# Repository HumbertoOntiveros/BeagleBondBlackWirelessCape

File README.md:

# BeagleBondBlackWirelessCape
A BeagleBone Black WIFI Cape
# Wi-Fi and BT/BLE connectivity Setup over SPI
## 1. Setup
### 1.1 Hardware Setup
In this setup, ESP board acts as a SPI peripheral and provides Wi-Fi capabilities to host. Please connect ESP peripheral to Beaglebone Black with jumper cables as mentioned below. It may be good to use small length cables to ensure signal integrity. Power ESP and BBB separately with a power supply that provide sufficient power. ESP can be powered through PC using micro-USB cable.

BBB pinout can be found [here!](https://beagleboard.org/support/bone101)

#### 1.1.1 ESP32 setup
| BBB pin label | BBB pin ID | ESP32 pin ID  | ESP32 pin function |
| --- | --- | --- | --- |
| P9_23 | 49 | 21 | GPIO_HANDSHAKE |
| P9_15 | 48 | 22 | GPIO_DATA_READY |
| SPI0_CS0 | P9_17 | 5 | CS |
| SPI0_SCLK | P9_22 | 18 | SCLK |
| SPI0_MISO D0 | P9_21 | 19 | MISO |
| SPI0_MOSI D1 | P9_18 | 23 | MOSI |
| P9_12 | 60 | RESET | RESET |

### 1.2 Beaglebone Black Software Setup
The SPI master driver is enabled by default on BBB OS. To disable it. 
```
cd host/linux/host_control/
./bbb_init.sh load_dtoverlay
```
the script will be update overlay for device tree to disable spi which used by default linux SPI driver.
The scrip will automatically reboot BBB after 10s to take effect. you could cancel.

## 2. Load ESP-Hosted Solution
### 2.1 Host Software
* Execute following commands in root directory of cloned ESP-Hosted repository on BBB
```sh
$ cd host/linux/host_control/
$ ./bbb_init.sh spi
```
* This script compiles and loads host driver on BBB. It also creates virtual serial interface `/dev/esps0` which is used as a control interface for Wi-Fi on ESP peripheral

### 2.2 ESP Peripheral Firmware
One can load pre-built release binaries on ESP peripheral or compile those from source. Below subsection explains Source Compilation methods due to this is a new commit for support BBB.

#### 2.2.1 Source Compilation
:warning:<code>Note: Please check [ESP-IDF Setup](Linux_based_readme.md#22-esp-idf-setup) and use appropriate ESP-IDF version</code>

* In root directory of ESP-Hosted repository, execute below command

```sh
$ cd esp/esp_driver/network_adapter
```

##### Using cmake

* :warning: `Set target if the ESP32-S2 or ESP32-C3 is being used. Skip if ESP32 is being used.`

```
$ idf.py set-target esp32
```
or
```
$ idf.py set-target esp32s2
```
or
```
$ idf.py set-target esp32c3
```

* Execute following command to configure project
```sh
$ idf.py menuconfig
```
* This will open project configuration window. To select SPI transport interface, navigate to `Example Configuration ->  Transport layer -> SPI interface -> select` and exit from menuconfig.

* For ESP32-C3, select chip revision in addition. Navigate to `Component config → ESP32C3-Specific → Minimum Supported ESP32-C3 Revision` and select chip version of ESP32-C3.

* Use below command to compile and flash the project. Replace <serial_port> with ESP peripheral's serial port.
```sh
$ idf.py -p <serial_port> build flash
```

## 3. Checking the Setup for SPI
Once ESP peripheral has a valid firmware and booted successfully, you should be able to see successful enumeration on BBB side as:
```
$ dmesg
[   96.439911] Bluetooth: Core ver 2.22
[   96.440145] NET: Registered protocol family 31
[   96.440153] Bluetooth: HCI device and connection manager initialized
[   96.440181] Bluetooth: HCI socket layer initialized
[   96.440195] Bluetooth: L2CAP socket layer initialized
[   96.440261] Bluetooth: SCO socket layer initialized
[  196.746813] esp32_spi: loading out-of-tree module taints kernel.
[  196.755748] esp_reset, ESP32: Resetpin of Host is 60
[  196.755892] esp_reset, ESP32: Triggering ESP reset.
[  196.775022] ESP32 peripheral is registered to SPI bus [0],chip select [0], SPI Clock [10]
[  199.310809] 
               Received INIT event from ESP32 peripheral
[  199.310839] EVENT: 2
[  199.310853] EVENT: 1
[  199.310857] EVENT: 0
[  199.310864] ESP peripheral capabilities: 0x78
[  200.155504] Bluetooth: BNEP (Ethernet Emulation) ver 1.3
[  200.155519] Bluetooth: BNEP filters: protocol multicast
[  200.155551] Bluetooth: BNEP socket layer initialized
[  200.699800] Bluetooth: RFCOMM TTY layer initialized
[  200.699842] Bluetooth: RFCOMM socket layer initialized
[  200.699906] Bluetooth: RFCOMM ver 1.11
```

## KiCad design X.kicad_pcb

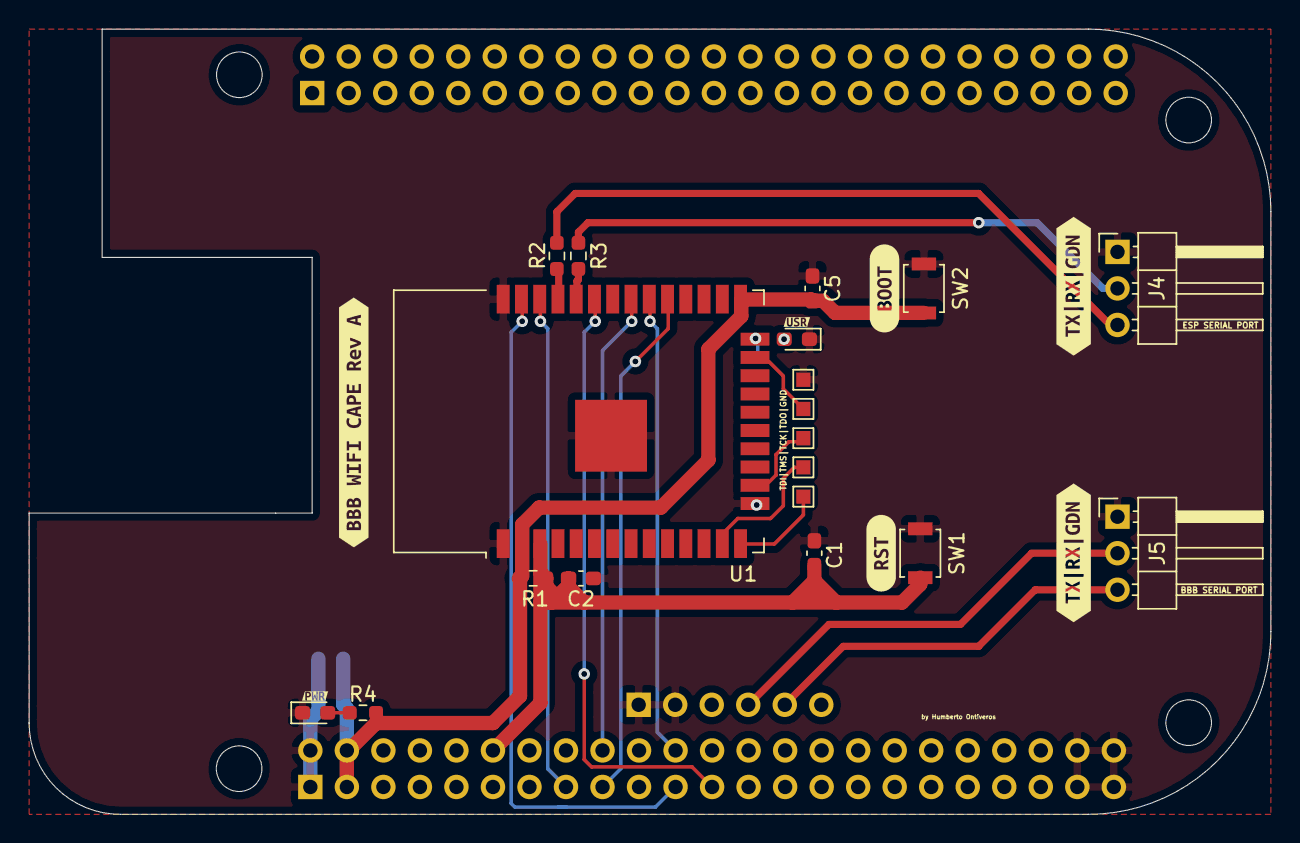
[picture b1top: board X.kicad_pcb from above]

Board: 2 copper layers, 86.4 x 54.6 mm, 33 parts (0 on the bottom side), 22 nets.

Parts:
C1, C2, C4, C5: 0.1uF(50v-10%); C_0603_1608Metric_Pad1.08x0.95mm_HandSolder
C3: 22uF(10V-20%); C_0603_1608Metric_Pad1.08x0.95mm_HandSolder
D1: POWER_LED; LED_0603_1608Metric_Pad1.05x0.95mm_HandSolder
D2: USER_LED; LED_0603_1608Metric_Pad1.05x0.95mm_HandSolder
J2: P8_CONN; BBB_CONN
J3: BBB_SP_CONN; PinSocket_1x06_P2.54mm_Vertical
J4: ESP_USB2TTL_CONN; PinHeader_1x03_P2.54mm_Horizontal
J5: BBB_USB2TTL_CONN; PinHeader_1x03_P2.54mm_Horizontal
J6: P9_CONN; BBB_CONN
R1, R6: 10K(5%); R_0603_1608Metric_Pad0.98x0.95mm_HandSolder
R2, R3: 0R(5%); R_0603_1608Metric_Pad0.98x0.95mm_HandSolder
R4, R5: 2K(5%); R_0603_1608Metric_Pad0.98x0.95mm_HandSolder
SW1: RST_SW
SW2: BOOT_SW; Boot_SW
TP1, TP2, TP3, TP4, TP5: TestPoint; TestPoint_Pad_1.0x1.0mm
U1: ESP32-WROOM-32D; ESP32-WROOM-32
kibuzzard-64DF0CF9, kibuzzard-64DF05EC, kibuzzard-64DF05EC#2, kibuzzard-64DF07FE, kibuzzard-64DF08E2, kibuzzard-64DF0500, kibuzzard-64DF0546: G***; label

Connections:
/IO2: R5.1, R6.2, U1.24
/TCK: TP3.1, U1.16
/TDI: TP4.1, U1.14
/TDO: TP2.1, U1.23
/TMS: TP5.1, U1.13
EN: C1.1, C2.1, J6.12, R1.2, SW1.2, U1.3
GND: C1.2, C2.2, C3.1, C4.1, C5.2, D1.1, D2.1, J3.1, J3.2, J4.1, J5.1, J6.1, J6.2, J6.43, J6.44, J6.45, J6.46, R6.1, SW1.1, SW2.2, TP1.1, U1.1, U1.15, U1.38, U1.39
GPIO_DATA_READY: J6.15, U1.36
GPIO_HANDSHAKE: J6.23, U1.33
IO0: C3.2, C4.2, C5.1, J6.3, J6.4, R1.1, R4.1, SW2.1, U1.2, U1.25
unnamed: D1.2, R4.2
unnamed: D2.2, R5.2
unnamed: J3.4, J5.2
unnamed: J3.5, J5.3
unnamed: R2.2, U1.35
unnamed: R3.2, U1.34
RXD: J4.2, R3.1
SPI0_CS0: J6.17, U1.29
SPI0_MISO: J6.21, U1.37
SPI0_MOSI: J6.18, U1.31
SPI0_SCLK: J6.22, U1.30
TXD: J4.3, R2.1

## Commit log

2023-08-22 License & README added
2023-08-24 some extra files no needed, deleted.
2023-08-24 Update README.md
    Update README.md
